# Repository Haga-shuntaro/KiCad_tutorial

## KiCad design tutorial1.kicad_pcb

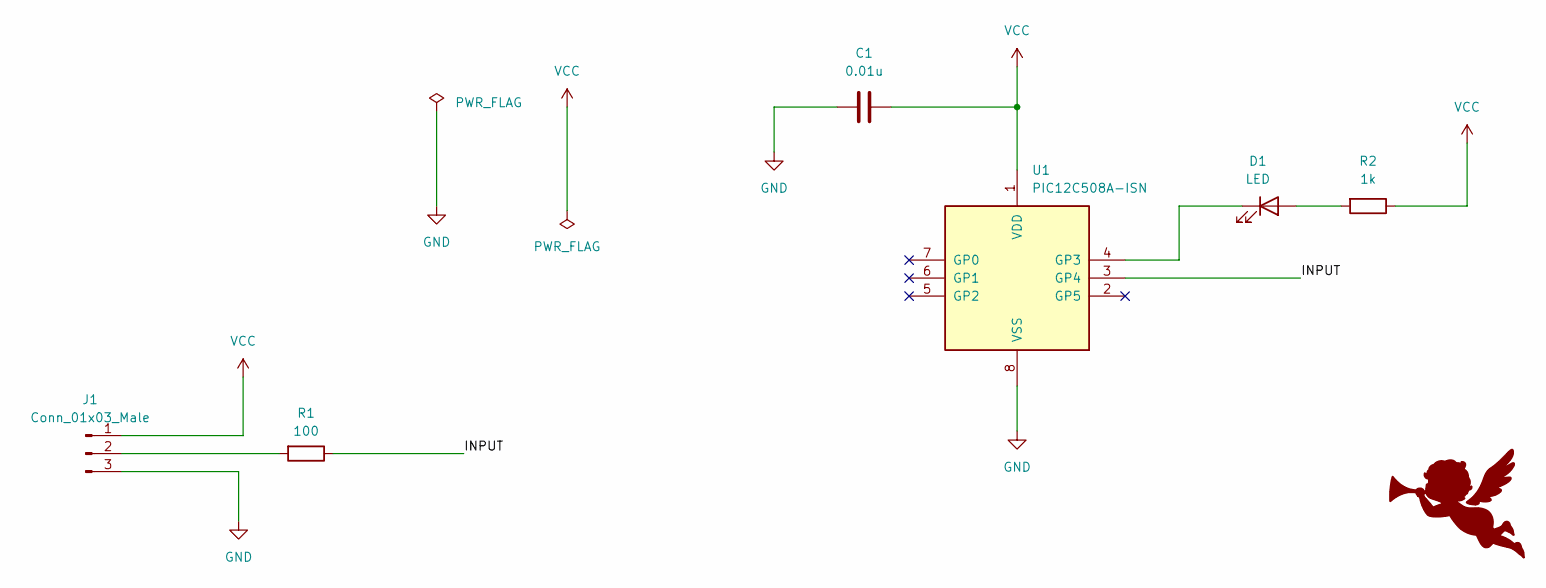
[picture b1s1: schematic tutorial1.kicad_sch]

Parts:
C1: 0.01u; C_0603_1608Metric_Pad1.08x0.95mm_HandSolder
D1: LED; LED_0603_1608Metric_Pad1.05x0.95mm_HandSolder
J1: Conn_01x03_Male; PinHeader_1x03_P2.54mm_Vertical
R1: 100; R_0603_1608Metric_Pad0.98x0.95mm_HandSolder
R2: 1k; R_0603_1608Metric_Pad0.98x0.95mm_HandSolder
U1: PIC12C508A-ISN; SOIC-8_3.9x4.9mm_P1.27mm

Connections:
/INPUT: R1.1, U1.3 (GP4)
GND: C1.2, J1.3, U1.8 (VSS)
unnamed: D1.1 (K), U1.4 (GP3)
unnamed: D1.2 (A), R2.2
unnamed: J1.2, R1.2
VCC: C1.1, J1.1, R2.1, U1.1 (VDD)

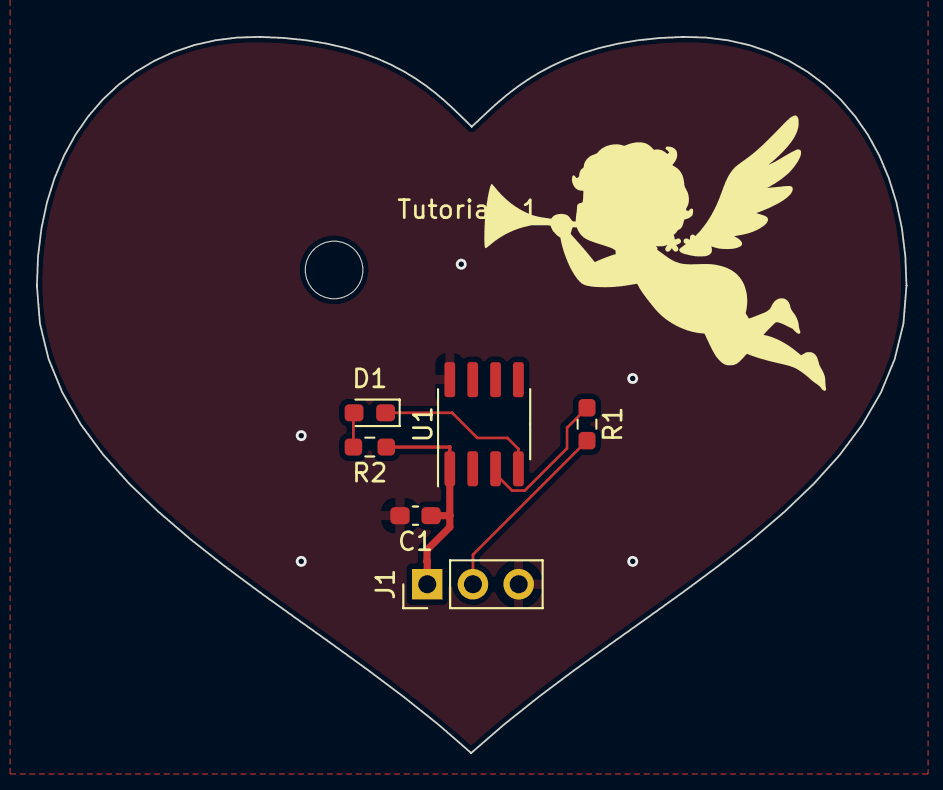
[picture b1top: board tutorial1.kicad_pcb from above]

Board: 2 copper layers, 48.3 x 39.8 mm, 7 parts (0 on the bottom side), 6 nets.

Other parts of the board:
MH1: MountingHole_3.2mm_M3

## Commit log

2022-08-11 #start:関連ファイルを追加
2022-08-12 #make:作業に伴う関連ファイルのアップデート
2022-08-12 #add:回路一つ分でのガーバーデータを作成・追加
2022-08-12 #add:面付け関連ファイルを作成・追加
2022-08-12 #add:gitignoreを追加
2022-08-13 #add:イメージファイルの作成方法について学習
2022-08-13 #update:実習に伴う更新
